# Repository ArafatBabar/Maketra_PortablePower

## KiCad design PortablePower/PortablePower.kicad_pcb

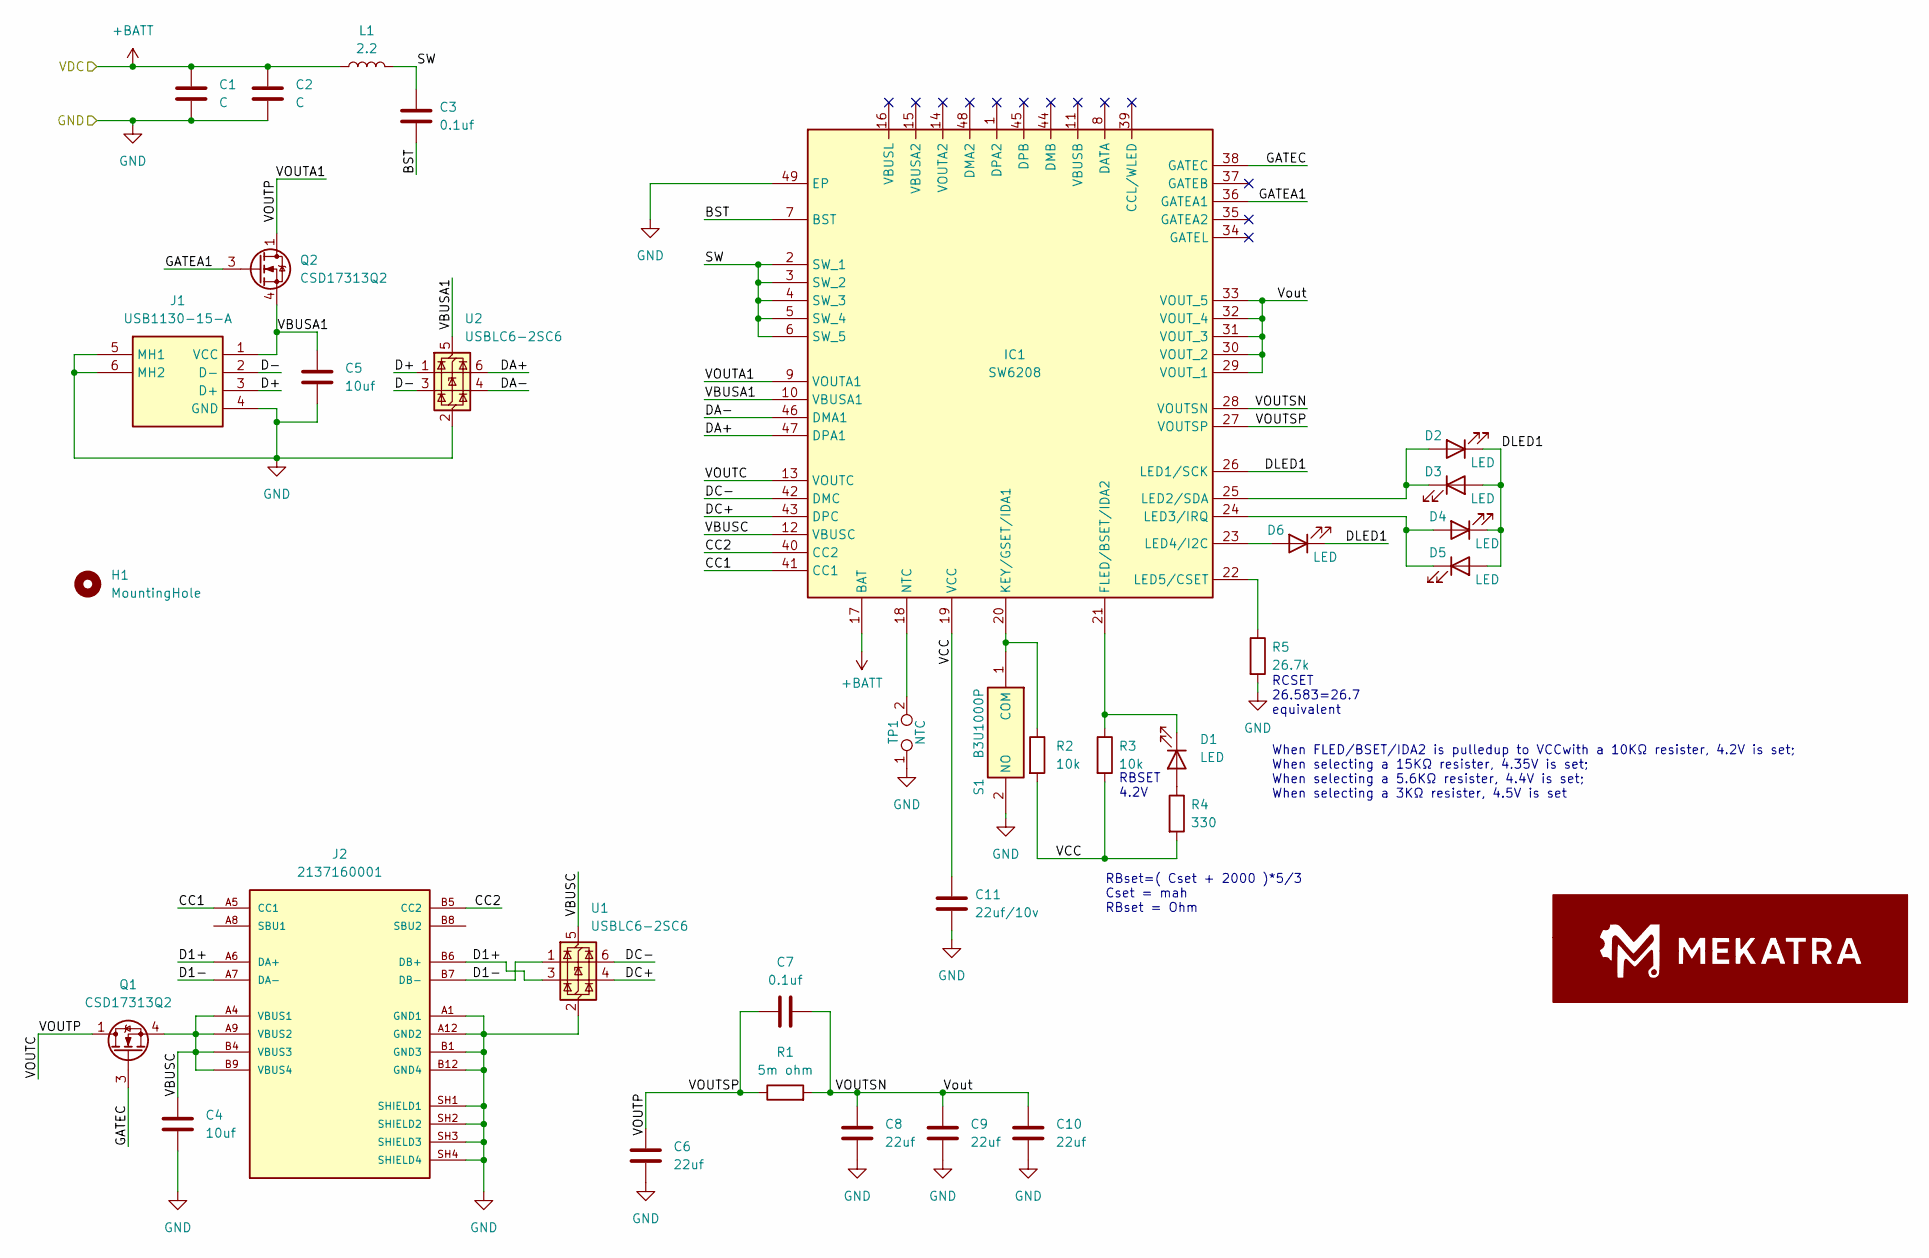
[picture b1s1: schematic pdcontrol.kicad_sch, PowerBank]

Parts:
C1, C2: C; C_1206_3216Metric_Pad1.33x1.80mm_HandSolder
C3, C7: 0.1uf; C_0603_1608Metric_Pad1.08x0.95mm_HandSolder
C4, C5: 10uf; C_1210_3225Metric_Pad1.33x2.70mm_HandSolder
C6, C8, C9, C10: 22uf; C_1210_3225Metric_Pad1.33x2.70mm_HandSolder
C11: 22uf/10v; C_0603_1608Metric_Pad1.08x0.95mm_HandSolder
D1, D2, D3, D4, D5, D6: LED; LED_1206_3216Metric_Pad1.42x1.75mm_HandSolder
H1: MountingHole; MountingHole_2.2mm_M2
IC1: SW6208; QFN40P600X600X80-49N; Manufacturer_Part_Number SW6208
J1: USB1130-15-A; USB113015A; Manufacturer_Part_Number USB1130-15-A; Mouser Part Number 640-USB1130-15-A
J2: 2137160001; MOLEX_2137160001; PARTREV B
L1: 2.2; L_Vishay_IHLP-5050
Q1, Q2: CSD17313Q2; Texas_DQK
R1: 5m ohm; R_2512_6332Metric_Pad1.40x3.35mm_HandSolder
R2, R3: 10k; R_0603_1608Metric_Pad0.98x0.95mm_HandSolder
R4: 330; R_0805_2012Metric_Pad1.20x1.40mm_HandSolder
R5: 26.7k; R_0603_1608Metric_Pad0.98x0.95mm_HandSolder
S1: B3U1000P; B3U-1000P; Manufacturer_Part_Number B3U1000P
TP1: NTC; PinHeader_2x01_P2.00mm_Vertical
U1, U2: USBLC6-2SC6; SOT-23-6

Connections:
+BATT: C1.1, C2.1, IC1.17 (BAT), L1.1; also elsewhere on the board
/PD_Control/BST: C3.2, IC1.7 (BST)
/PD_Control/CC1: IC1.41 (CC1), J2.A5 (CC1)
/PD_Control/CC2: IC1.40 (CC2), J2.B5 (CC2)
/PD_Control/D1+: J2.A6 (DA+), J2.B6 (DB+), U1.3 (I/O2)
/PD_Control/D1-: J2.A7 (DA-), J2.B7 (DB-), U1.1 (I/O1)
/PD_Control/D+: J1.3 (D+), U2.1 (I/O1)
/PD_Control/D-: J1.2 (D-), U2.3 (I/O2)
/PD_Control/DA+: IC1.47 (DPA1), U2.6 (I/O1)
/PD_Control/DA-: IC1.46 (DMA1), U2.4 (I/O2)
/PD_Control/DC+: IC1.43 (DPC), U1.4 (I/O2)
/PD_Control/DC-: IC1.42 (DMC), U1.6 (I/O1)
/PD_Control/DLED1: D2.1 (K), D3.2 (A), D4.1 (K), D5.2 (A), D6.1 (K), IC1.26 (LED1/SCK)
/PD_Control/GATEA1: IC1.36 (GATEA1), Q2.3 (G)
/PD_Control/GATEC: IC1.38 (GATEC), Q1.3 (G)
/PD_Control/SW: C3.1, IC1.2 (SW_1), IC1.3 (SW_2), IC1.4 (SW_3), IC1.5 (SW_4), IC1.6 (SW_5), L1.2
/PD_Control/VBUSA1: C5.1, IC1.10 (VBUSA1), J1.1 (VCC), Q2.4 (S), Q2.7 (S), U2.5 (VBUS)
/PD_Control/VBUSC: C4.1, IC1.12 (VBUSC), J2.A4 (VBUS1), J2.A9 (VBUS2), J2.B4 (VBUS3), J2.B9 (VBUS4), Q1.4 (S), Q1.7 (S), U1.5 (VBUS)
/PD_Control/VCC: C11.1, IC1.19 (VCC), R2.2, R3.2, R4.2
/PD_Control/VOUTA1: C6.1, C7.2, IC1.9 (VOUTA1), IC1.13 (VOUTC), IC1.27 (VOUTSP), Q1.1 (D), Q1.2 (D), Q1.5 (D), Q1.6 (D), Q1.8 (D), Q2.1 (D), Q2.2 (D), Q2.5 (D), Q2.6 (D), Q2.8 (D), R1.1
/PD_Control/VOUTSN: C7.1, C8.1, C9.1, C10.1, IC1.28 (VOUTSN), IC1.29 (VOUT_1), IC1.30 (VOUT_2), IC1.31 (VOUT_3), IC1.32 (VOUT_4), IC1.33 (VOUT_5), R1.2
GND: C1.2, C2.2, C4.2, C5.2, C6.2, C8.2, C9.2, C10.2, C11.2, IC1.49 (EP), J1.4 (GND), J1.5 (MH1), J1.6 (MH2), J2.A1 (GND1), J2.A12 (GND2), J2.B1 (GND3), J2.B12 (GND4), J2.SH1 (SHIELD1), J2.SH2 (SHIELD2), J2.SH3 (SHIELD3), J2.SH4 (SHIELD4), R5.2, S1.2 (NO), TP1.1, U1.2 (GND), U2.2 (GND); also elsewhere on the board
unnamed: D1.2 (A), R4.1
unnamed: D1.1 (K), IC1.21 (FLED/BSET/IDA2), R3.1
unnamed: D2.2 (A), D3.1 (K), IC1.25 (LED2/SDA)
unnamed: D4.2 (A), D5.1 (K), IC1.24 (LED3/IRQ)
unnamed: D6.2 (A), IC1.23 (LED4/I2C)
unnamed: IC1.20 (KEY/GSET/IDA1), R2.1, S1.1 (COM)
unnamed: IC1.22 (LED5/CSET), R5.1
unnamed: IC1.18 (NTC), TP1.2

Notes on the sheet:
RBset=( Cset + 2000 )*5/3 Cset = mah RBset = Ohm
RCSET 26.583=26.7 equivalent
When FLED/BSET/IDA2 is pulledup to VCCwith a 10KΩ resister, 4.2V is set; When selecting a 15KΩ resister, 4.35V is set; When selecting a 5.6KΩ resister, 4.4V is set; When selecting a 3KΩ resister, 4.5V is set
RBSET 4.2V

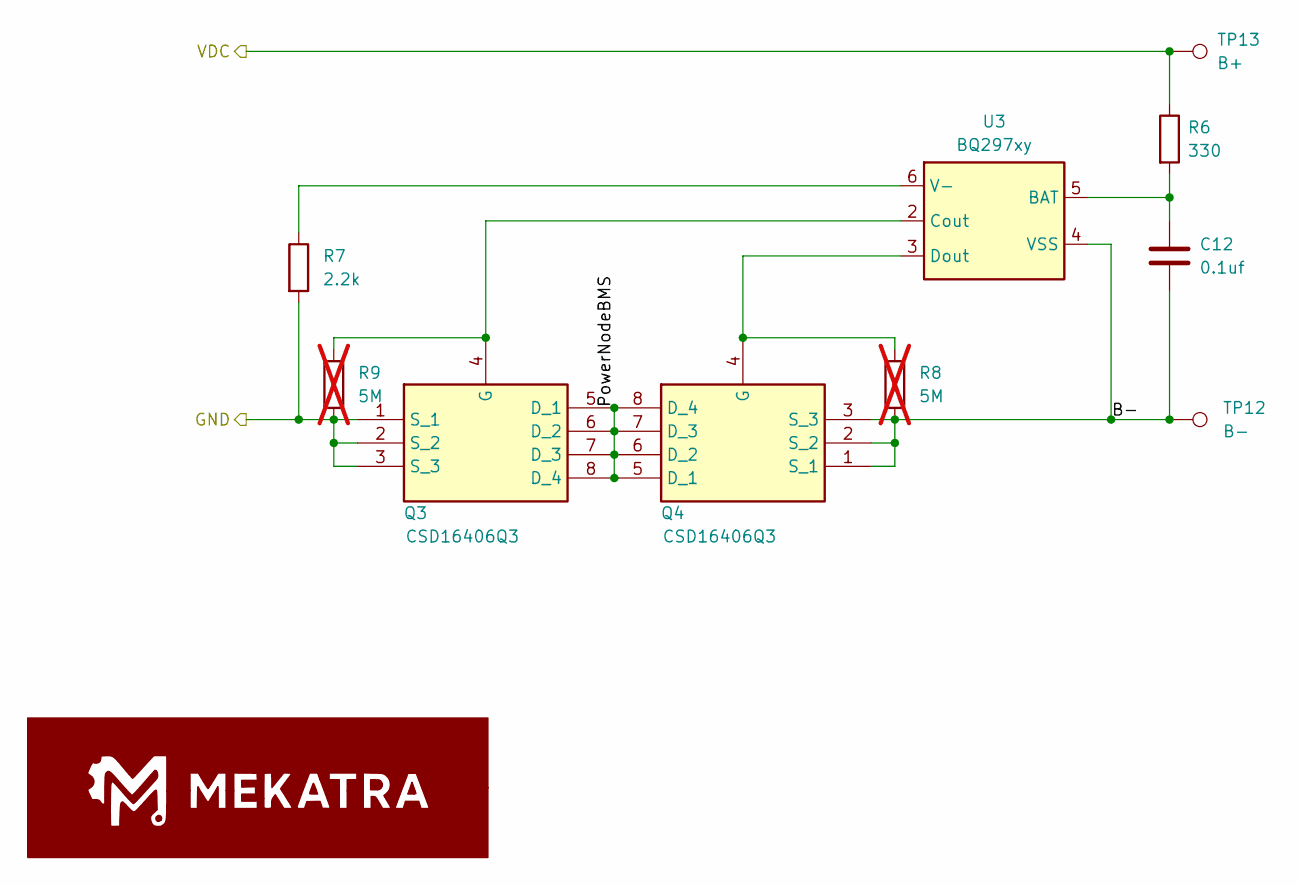
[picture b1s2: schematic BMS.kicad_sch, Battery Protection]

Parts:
C12: 0.1uf; C_0603_1608Metric_Pad1.08x0.95mm_HandSolder
Q3, Q4: CSD16406Q3; DQG_VSON-CLIP; Manufacturer_Part_Number CSD16406Q3; Mouser Part Number 595-CSD16406Q3
R6: 330; R_0805_2012Metric_Pad1.20x1.40mm_HandSolder
R7: 2.2k; R_0603_1608Metric_Pad0.98x0.95mm_HandSolder
R8, R9: 5M; R_1206_3216Metric_Pad1.30x1.75mm_HandSolder; not fitted
TP12: B-; TestPoint_Pad_D4.0mm
TP13: B+; TestPoint_Pad_4.0x4.0mm
U3: BQ297xy; WSON-6_1.5x1.5mm_P0.5mm

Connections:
+BATT: R6.1, TP13.1; also elsewhere on the board
/BMS/B-: C12.2, Q4.1 (S_1), Q4.2 (S_2), Q4.3 (S_3), R8.2, TP12.1, U3.4 (VSS)
/BMS/PowerNodeBMS: Q3.5 (D_1), Q3.6 (D_2), Q3.7 (D_3), Q3.8 (D_4), Q3.9, Q4.5 (D_1), Q4.6 (D_2), Q4.7 (D_3), Q4.8 (D_4), Q4.9
GND: Q3.1 (S_1), Q3.2 (S_2), Q3.3 (S_3), R7.2, R9.2; also elsewhere on the board
unnamed: Q3.4 (G), R9.1, U3.2 (Cout)
unnamed: Q4.4 (G), R8.1, U3.3 (Dout)
unnamed: C12.1, R6.2, U3.5 (BAT)
unnamed: R7.1, U3.6 (V-)

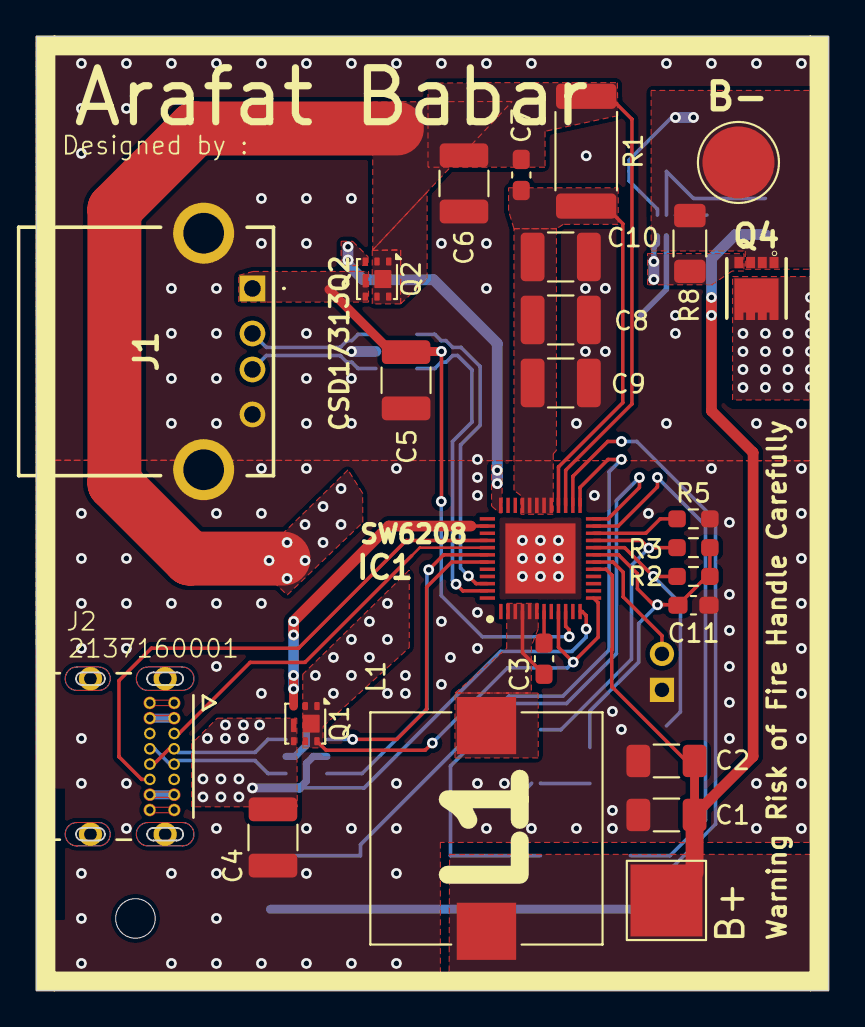
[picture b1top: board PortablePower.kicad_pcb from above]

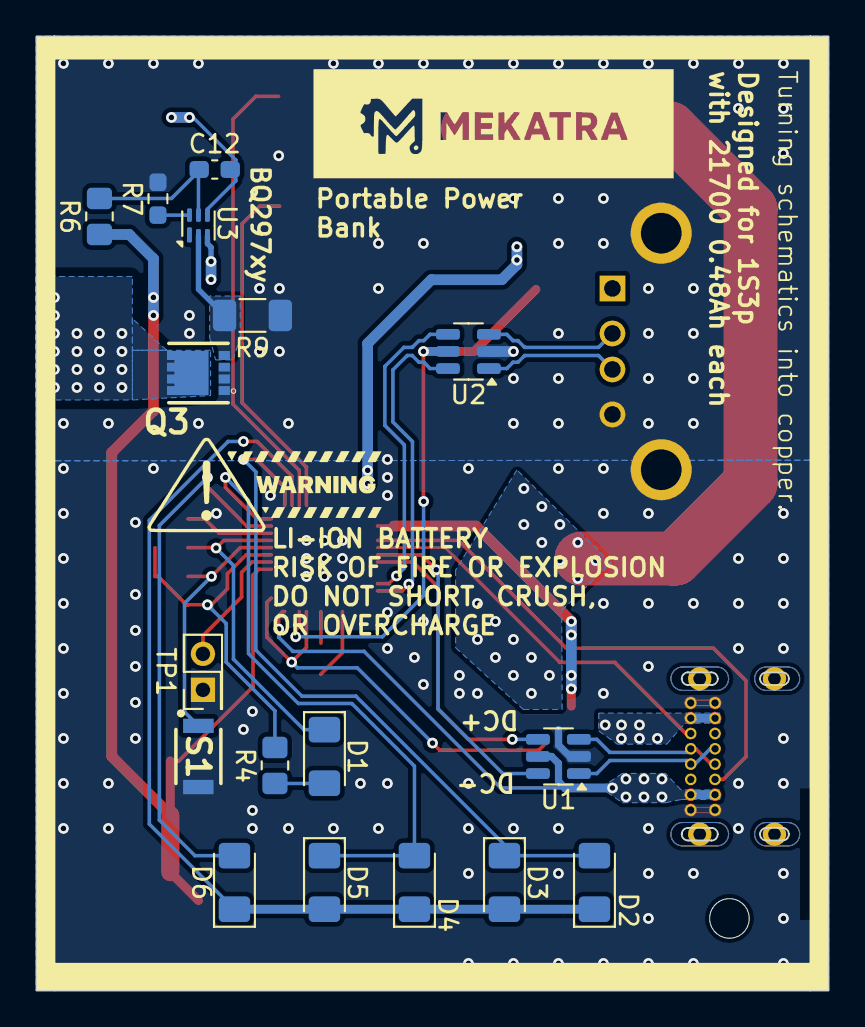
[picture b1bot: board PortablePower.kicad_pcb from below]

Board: 2 copper layers, 44.0 x 53.0 mm, 43 parts (17 on the bottom side), 36 nets.

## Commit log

2026-01-10 design considerations
2026-01-10 almost done with pd control
2026-01-10 schematic complete
2026-01-11 before done schematic
2026-01-12 randome one
2026-01-12 halfway through pd everything
2026-01-13 mostly done on pd layout
2026-01-13 pc done
2026-01-13 added logo
2026-01-13 mostly ddone
2026-01-14 mostly done
2026-01-14 minor change
2026-01-24 final update
